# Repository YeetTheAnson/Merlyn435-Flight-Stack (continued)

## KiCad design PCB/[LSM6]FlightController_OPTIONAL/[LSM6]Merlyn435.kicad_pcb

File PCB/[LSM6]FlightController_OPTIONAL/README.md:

Almomst identical to the MPU6500 version of the board, but the footprint is changed to support LSM6 (LSM6DSK320X/LSM6DSV16X/LSM6DSO/LSM6DSOX) series gyro which has superior noise rejection compared to MPU6500 in high vibration environments.

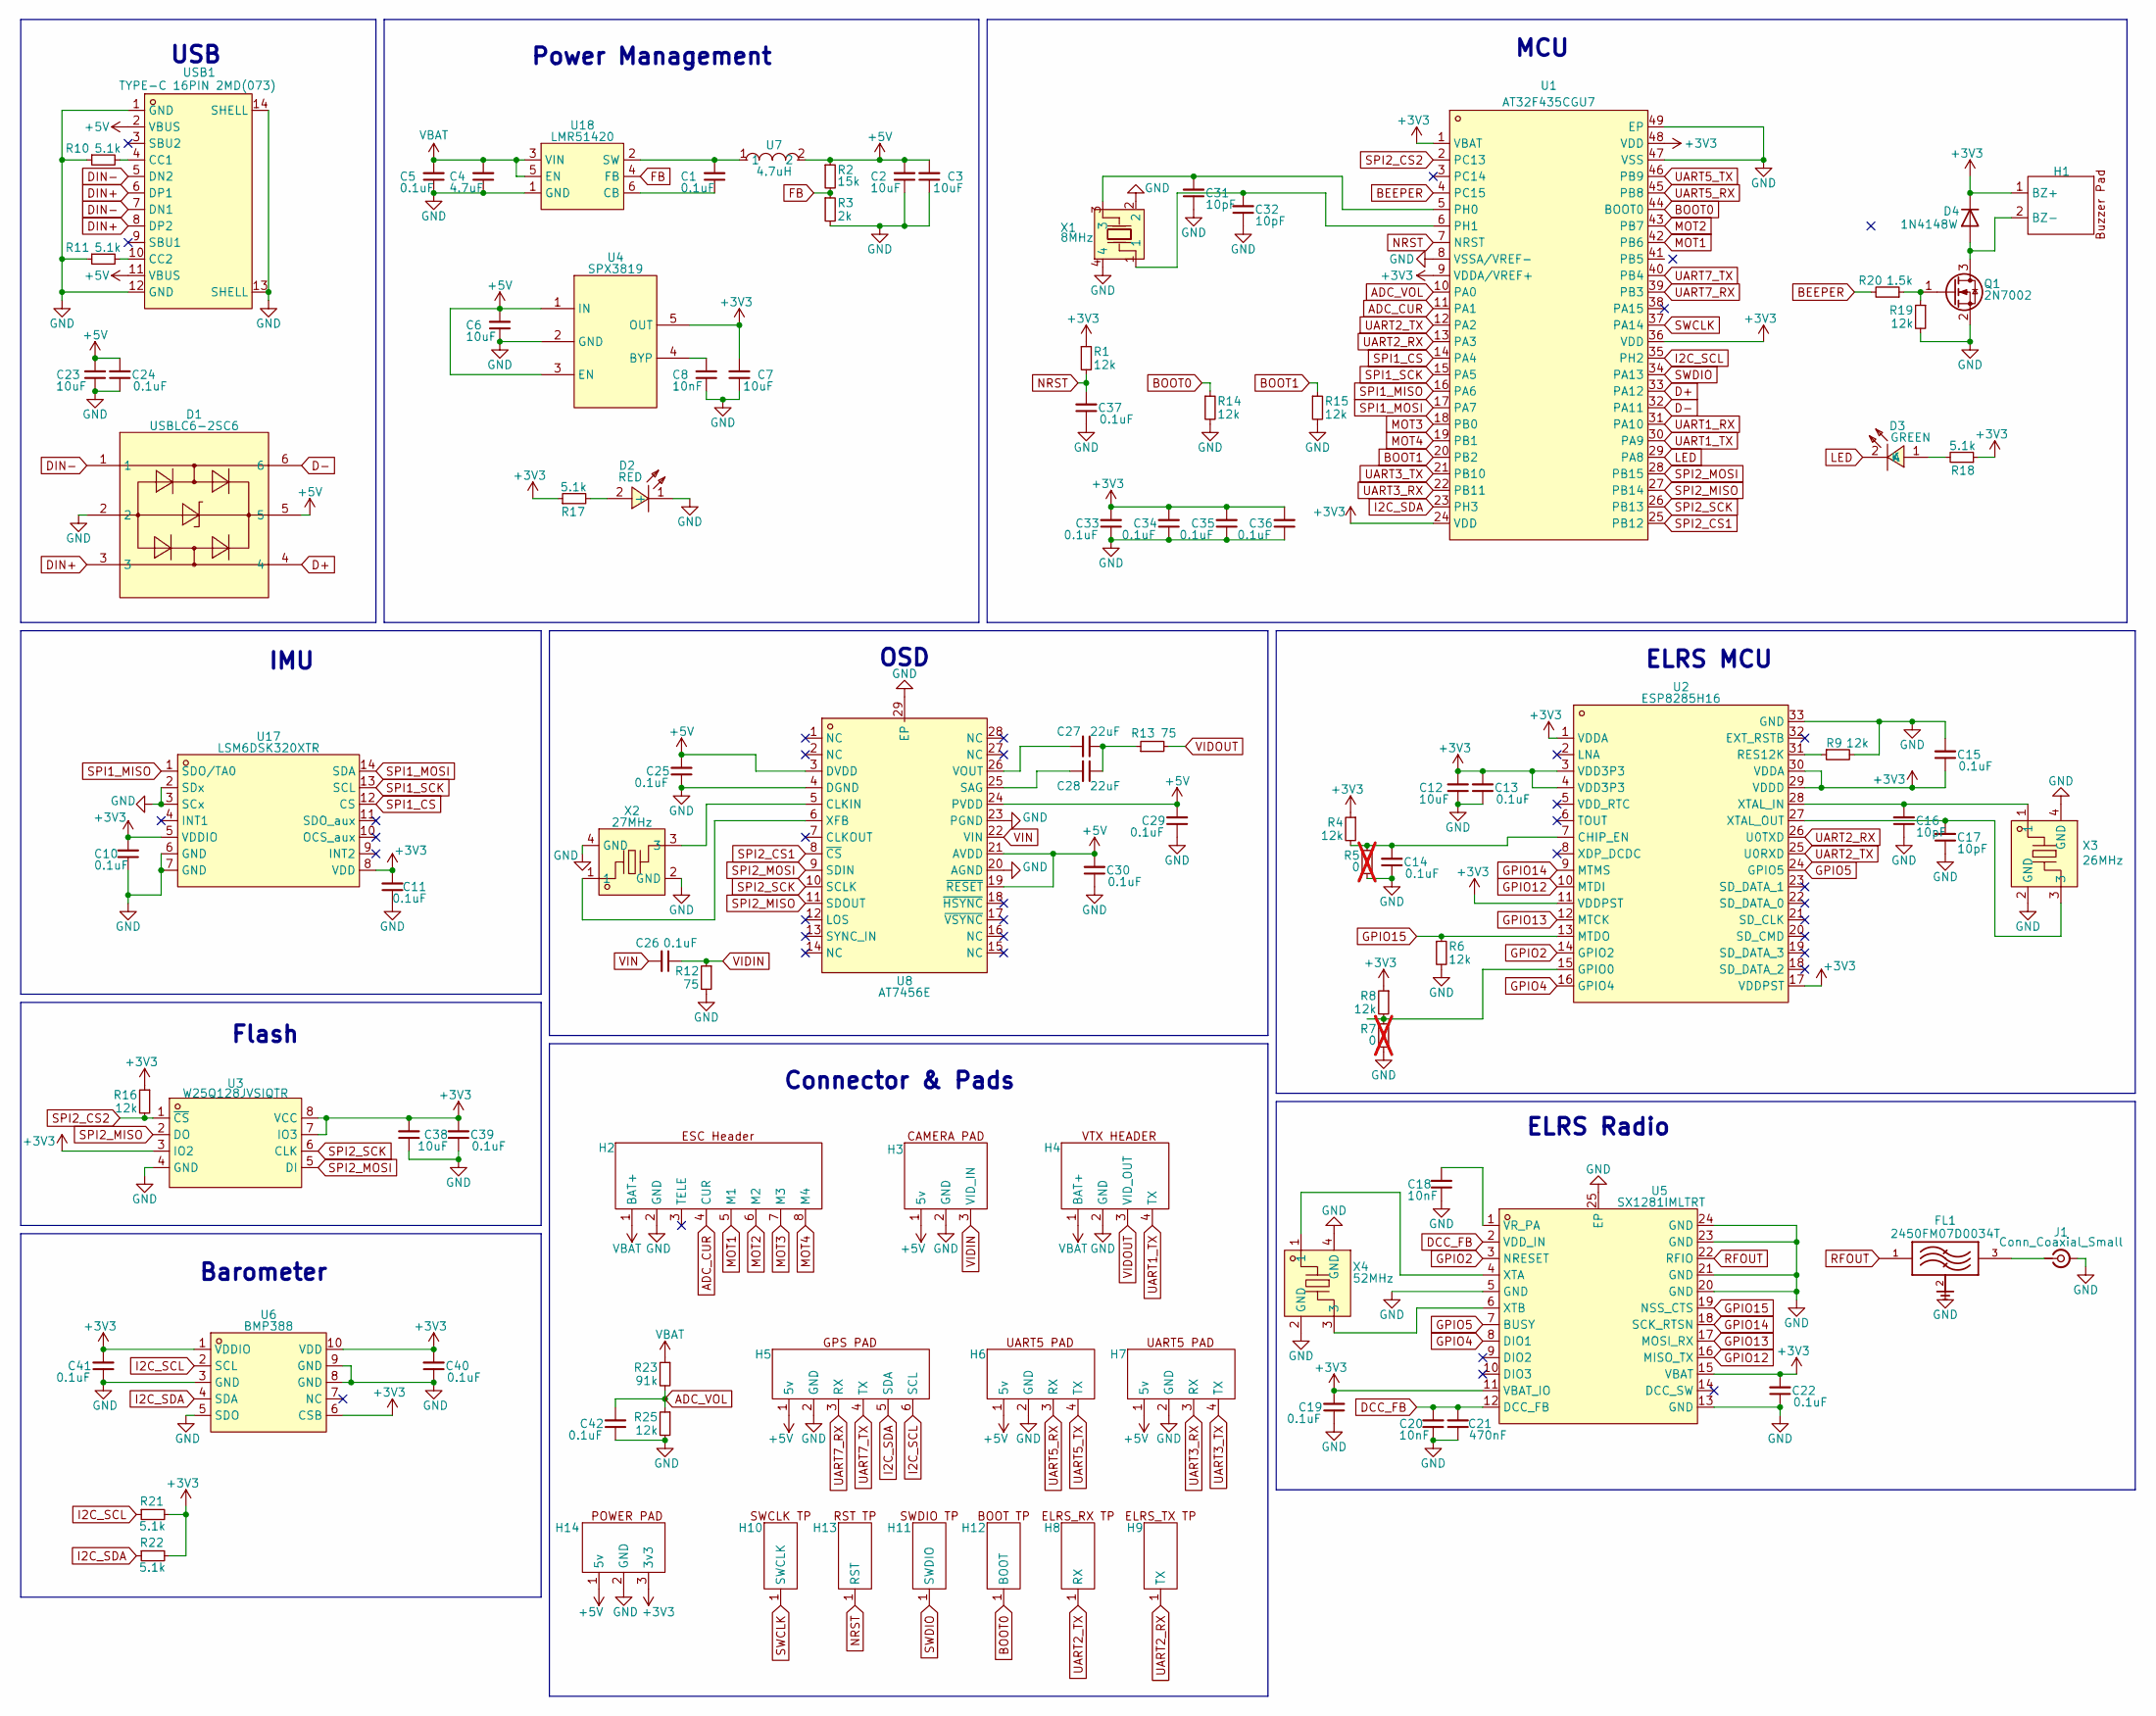
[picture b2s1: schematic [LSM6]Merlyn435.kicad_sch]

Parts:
C1, C5, C10, C11, C13, C14, C15, C19, C22, C24, C25, C26, C29, C30, C33, C34, C35, C36, C37, C39, C40, C41, C42: 0.1uF; C_0402_1005Metric; LCSC Part C307331
C2, C3, C6, C7: 10uF; C_0603_1608Metric; LCSC Part C96446
C4: 4.7uF; C_1206_3216Metric; LCSC Part C29823
C8, C18, C20: 10nF; C_0402_1005Metric; LCSC Part C15195
C12, C23, C38: 10uF; C_0402_1005Metric; LCSC Part C15525
C16, C17, C31, C32: 10pF; C_0402_1005Metric; LCSC Part C32949
C21: 470nF; C_0402_1005Metric; LCSC Part C47339
C27, C28: 22uF; C_0805_2012Metric; LCSC Part C45783
D1: USBLC6-2SC6; SOT-23-6_L2.9-W1.6-P0.95-LS2.8-BL; MPN USBLC6-2SC6; LCSC Part C7519
D2: RED; LED0805-RD; MPN NCD0805R1; LCSC Part C84256
D3: GREEN; LED0805-R-RD; MPN KT-0805G; LCSC Part C2297
D4: 1N4148W; D_SOD-123
FL1: 2450FM07D0034T; FIL_2450FM07D0034T; PARTREV 1.2
H1: Buzzer Pad
H2: ESC Header
H3: Camera Pad
H4: VTX Pad
H5: GPS Pad
H6: UART5 PAD
H7: UART3 PAD
H8: ELRS_RX TP
H9: ELRS_TX TP
H10: SWCLK TP
H11: SWDIO TP
H12: SWD_BOOT TP
H13: SWD_RST TP
H14: Power Pad
J1: Conn_Coaxial_Small; UFL
Q1: 2N7002; SOT-23
R1, R4, R6, R8, R9, R14, R15, R16, R19, R25: 12k; R_0402_1005Metric; LCSC Part C25752
R2: 15k; R_0402_1005Metric; LCSC Part C25756
R3: 2k; R_0402_1005Metric; LCSC Part C4109
R5, R7: 0; R_0402_1005Metric; not fitted
R10, R11, R17, R18, R21, R22: 5.1k; R_0402_1005Metric; LCSC Part C25905
R12, R13: 75; R_0402_1005Metric; LCSC Part C25133
R20: 1.5k; R_0402_1005Metric; LCSC Part C25867
R23: 91k; R_0603_1608Metric; LCSC Part C23265
U1: AT32F435CGU7; QFN-48_L6.0-W6.0-P0.40-TL-EP3.2; MPN AT32F435CGU7; LCSC Part C5178937
U2: ESP8285H16; QFN-32_L5.0-W5.0-P0.50-TL-EP3.7; MPN ESP8285H16; LCSC Part C967019
U3: W25Q128JVSIQTR; SOIC-8_L5.3-W5.3-P1.27-LS8.0-BL; MPN W25Q128JVSIQ; LCSC Part C97521
U4: SPX3819; SOT-23-5_L3.0-W1.7-P0.95-LS2.8-BL; MPN SPX3819M5-L-3-3/TR; LCSC Part C9055
U5: SX1281IMLTRT; QFN-24_L4.0-W4.0-P0.50-TL-EP2.6; MPN SX1281IMLTRT; LCSC Part C2151551
U6: BMP388; LGA-10_L2.0-W2.0-P0.50-BL; MPN BMP388(TOKMAS); LCSC Part C54582187
U7: 4.7uH; IND-SMD_L4.4-W4.2; MPN APH0420T4R7M; LCSC Part C5349668
U8: AT7456E; TSSOP-28_L9.7-W4.4-P0.65-LS6.4-BL-EP-2; MPN AT7456E; LCSC Part C82351
U17: LSM6DSK320XTR; LGA-14_L3.0-W2.5-P0.50-TL; MPN LSM6DSK320XTR; LCSC Part C53025794
U18: LMR51420; SOT-23-6_L2.9-W1.6-P0.95-LS2.9-BL; MPN LMR51420YDDCR; LCSC Part C5383002
USB1: TYPE-C 16PIN 2MD(073); USB-TYPE-C-SMD_TYPE-C-16P-QTWT; LCSC Part C5187472
X1: 8MHz; CRYSTAL-SMD_4P-L3.2-W2.5-BL; MPN TAXM8M4RDBCCT2T; LCSC Part C400090
X2: 27MHz; CRYSTAL-SMD_4P-L2.0-W1.6-BL; MPN 7D027000I01; LCSC Part C648950
X3: 26MHz; CRYSTAL-SMD_4P-L2.0-W1.6-BL; MPN XL7EL89CMI-111YLC-26M; LCSC Part C19272774
X4: 52MHz; CRYSTAL-SMD_4P-L2.0-W1.6-BL; MPN XC21M4-52.000-F10NNHPL; LCSC Part C3034316

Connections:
+3V3: C7.2, C10.2, C11.2, C12.2, C13.2, C15.1, C19.2, C22.2, C33.2, C34.2, C35.2, C36.2, C38.2, C39.2, C40.2, C41.2, D4.1 (K), H1.1 (BZ+), H14.3 (3v3), R1.1, R4.1, R8.1, R16.1, R17.1, R18.1, R21.2, R22.2, U1.1 (VBAT), U1.9 (VDDA/VREF+), U1.24 (VDD), U1.36 (VDD), U1.48 (VDD), U2.1 (VDDA), U2.3 (VDD3P3), U2.4 (VDD3P3), U2.11 (VDDPST), U2.17 (VDDPST), U2.29 (VDDD), U2.30 (VDDA), U3.3 (IO2), U3.7 (IO3), U3.8 (VCC), U4.5 (OUT), U5.11 (VBAT_IO), U5.15 (VBAT), U6.1 (VDDIO), U6.6 (CSB), U6.10 (VDD), U17.5 (VDDIO), U17.8 (VDD)
+5V: C2.2, C3.2, C6.2, C23.2, C24.2, C25.2, C29.2, C30.2, D1.5, H3.1 (5v), H5.1 (5v), H6.1 (5v), H7.1 (5v), H14.1 (5v), R2.1, U4.1 (IN), U4.3 (EN), U7.2, U8.3 (DVDD), U8.19 (~RESET), U8.21 (AVDD), U8.24 (PVDD), USB1.2 (VBUS), USB1.11 (VBUS)
ADC_CUR: H2.4 (CUR), U1.11 (PA1)
ADC_VOL: C42.2, R23.2, R25.1, U1.10 (PA0)
BEEPER: R20.2, U1.4 (PC15)
BOOT0: H12.1 (BOOT), R14.1, U1.44 (BOOT0)
BOOT1: R15.1, U1.20 (PB2)
D+: D1.4, U1.33 (PA12)
D-: D1.6, U1.32 (PA11)
DCC_FB: C20.2, C21.2, U5.2 (VDD_IN), U5.12 (DCC_FB)
DIN+: D1.3, USB1.6 (DP1), USB1.8 (DP2)
DIN-: D1.1, USB1.5 (DN2), USB1.7 (DN1)
FB: R2.2, R3.1, U18.4 (FB)
GND: C2.1, C3.1, C4.1, C5.1, C6.1, C7.1, C8.1, C10.1, C11.1, C12.1, C13.1, C14.1, C15.2, C16.1, C17.1, C18.1, C19.1, C20.1, C21.1, C22.1, C23.1, C24.1, C25.1, C29.1, C30.1, C31.1, C32.1, C33.1, C34.1, C35.1, C36.1, C37.1, C38.1, C39.1, C40.1, C41.1, C42.1, D1.2, D2.1 (-), FL1.2, FL1.4, H2.2 (GND), H3.2 (GND), H4.2 (GND), H5.2 (GND), H6.2 (GND), H7.2 (GND), H14.2 (GND), J1.2 (Ext), Q1.2 (S), R3.2, R5.2, R6.2, R7.2, R9.2, R10.1, R11.1, R12.2, R14.2, R15.2, R19.2, R25.2, U1.8 (VSSA/VREF-), U1.47 (VSS), U1.49 (EP), U2.33 (GND), U3.4 (GND), U4.2 (GND), U5.5 (GND), U5.13 (GND), U5.20 (GND), U5.21 (GND), U5.23 (GND), U5.24 (GND), U5.25 (EP), U6.3 (GND), U6.5 (SDO), U6.8 (GND), U6.9 (GND), U8.4 (DGND), U8.20 (AGND), U8.23 (PGND), U8.29 (EP), U17.2 (SDx), U17.3 (SCx), U17.6 (GND), U17.7 (GND), U18.1 (GND), USB1.1 (GND), USB1.12 (GND), USB1.13 (SHELL), USB1.14 (SHELL), X1.2, X1.4, X2.2 (GND), X2.4 (GND), X3.2 (GND), X3.4 (GND), X4.2 (GND), X4.4 (GND)
GPIO2: U2.14 (GPIO2), U5.3 (NRESET)
GPIO4: U2.16 (GPIO4), U5.8 (DIO1)
GPIO5: U2.24 (GPIO5), U5.7 (BUSY)
GPIO12: U2.10 (MTDI), U5.16 (MISO_TX)
GPIO13: U2.12 (MTCK), U5.17 (MOSI_RX)
GPIO14: U2.9 (MTMS), U5.18 (SCK_RTSN)
GPIO15: R6.1, U2.13 (MTDO), U5.19 (NSS_CTS)
I2C_SCL: H5.6 (SCL), R21.1, U1.35 (PH2), U6.2 (SCL)
I2C_SDA: H5.5 (SDA), R22.1, U1.23 (PH3), U6.4 (SDA)
LED: D3.2 (K), U1.29 (PA8)
MOT1: H2.5 (M1), U1.42 (PB6)
MOT2: H2.6 (M2), U1.43 (PB7)
MOT3: H2.7 (M3), U1.18 (PB0)
MOT4: H2.8 (M4), U1.19 (PB1)
NRST: C37.2, H13.1 (RST), R1.2, U1.7 (NRST)
unnamed: C27.1, C28.1, R13.1
unnamed: D2.2 (+), R17.2
unnamed: D3.1 (A), R18.2
unnamed: D4.2 (A), H1.2 (BZ-), Q1.3 (D)
unnamed: FL1.3, J1.1 (In)
unnamed: Q1.1 (G), R19.1, R20.1
unnamed: C31.2, U1.5 (PH0), X1.3
unnamed: C32.2, U1.6 (PH1), X1.1
unnamed: C14.2, R4.2, R5.1, U2.7 (CHIP_EN)
unnamed: R7.1, R8.2, U2.15 (GPIO0)
unnamed: R9.1, U2.31 (RES12K)
unnamed: C16.2, U2.28 (XTAL_IN), X3.1
unnamed: C17.2, U2.27 (XTAL_OUT), X3.3
unnamed: C8.2, U4.4 (BYP)
unnamed: C18.2, U5.1 (VR_PA)
unnamed: U5.4 (XTA), X4.1
unnamed: U5.6 (XTB), X4.3
unnamed: U8.5 (CLKIN), X2.3
unnamed: C28.2, U8.25 (SAG)
unnamed: C27.2, U8.26 (VOUT)
unnamed: U8.6 (XFB), X2.1
unnamed: C1.1, U18.6 (CB)
unnamed: C1.2, U7.1, U18.2 (SW)
unnamed: R10.2, USB1.4 (CC1)
unnamed: R11.2, USB1.10 (CC2)
RFOUT: FL1.1, U5.22 (RFIO)
SPI1_CS: U1.14 (PA4), U17.12 (CS)
SPI1_MISO: U1.16 (PA6), U17.1 (SDO/TA0)
SPI1_MOSI: U1.17 (PA7), U17.14 (SDA)
SPI1_SCK: U1.15 (PA5), U17.13 (SCL)
SPI2_CS1: U1.25 (PB12), U8.8 (~CS)
SPI2_CS2: R16.2, U1.2 (PC13), U3.1 (~CS)
SPI2_MISO: U1.27 (PB14), U3.2 (DO), U8.11 (SDOUT)
SPI2_MOSI: U1.28 (PB15), U3.5 (DI), U8.9 (SDIN)
SPI2_SCK: U1.26 (PB13), U3.6 (CLK), U8.10 (SCLK)
SWCLK: H10.1 (SWCLK), U1.37 (PA14)
SWDIO: H11.1 (SWDIO), U1.34 (PA13)
UART1_RX: U1.31 (PA10)
UART1_TX: H4.4 (TX), U1.30 (PA9)
UART2_RX: H9.1 (TX), U1.13 (PA3), U2.26 (U0TXD)
UART2_TX: H8.1 (RX), U1.12 (PA2), U2.25 (U0RXD)
UART3_RX: H7.3 (RX), U1.22 (PB11)
UART3_TX: H7.4 (TX), U1.21 (PB10)
UART5_RX: H6.3 (RX), U1.45 (PB8)
UART5_TX: H6.4 (TX), U1.46 (PB9)
UART7_RX: H5.3 (RX), U1.39 (PB3)
UART7_TX: H5.4 (TX), U1.40 (PB4)
VBAT: C4.2, C5.2, H2.1 (BAT+), H4.1 (BAT+), R23.1, U18.3 (VIN), U18.5 (EN)
VIDIN: C26.1, H3.3 (VID_IN), R12.1
VIDOUT: H4.3 (VID_OUT), R13.2
VIN: C26.2, U8.22 (VIN)

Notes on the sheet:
Barometer
USB
Power Management
ELRS Radio
Connector & Pads
MCU
ELRS MCU
OSD
IMU
Flash

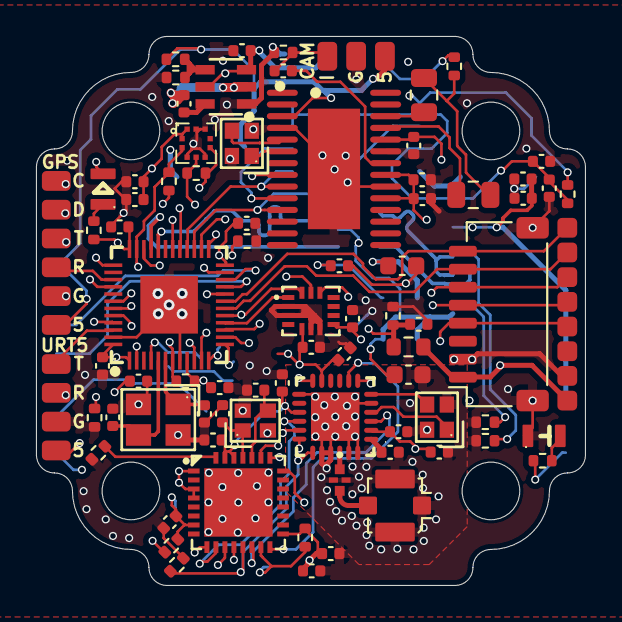
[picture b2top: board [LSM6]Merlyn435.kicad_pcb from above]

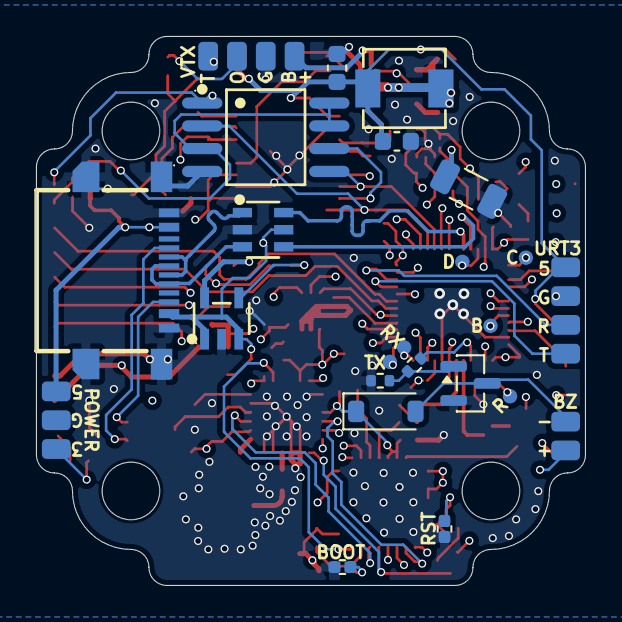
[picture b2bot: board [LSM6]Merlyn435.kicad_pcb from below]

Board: 4 copper layers, 30.5 x 30.5 mm, 101 parts (24 on the bottom side), 79 nets.

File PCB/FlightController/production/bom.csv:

Designator,Footprint,Quantity,Value,LCSC Part #
"C1, C10, C11, C13, C14, C15, C19, C22, C24, C25, C26, C29, C30, C33, C34, C35, C36, C37, C39, C40, C41, C42, C5",0402,23,0.1uF,C307331
"C12, C23, C38",0402,3,10uF,C15525
"C16, C17, C31, C32",0402,4,10pF,C32949
"C18, C20, C8, C9",0402,4,10nF,C15195
"C2, C3, C6, C7",0603,4,10uF,C96446
C21,0402,1,470nF,C47339
"C27, C28",0805,2,22uF,C45783
C4,1206,1,4.7uF,C29823 
D1,SOT-23-6_L2.9-W1.6-P0.95-LS2.8-BL,1,USBLC6-2SC6,C7519
D2,LED0805-RD,1,RED,C84256
D3,LED0805-R-RD,1,GREEN,C2297
D4,D_SOD-123,1,1N4148W,
H1,Buzzer Pad,1,~,
H10,SWCLK TP,1,~,
H11,SWDIO TP,1,~,
H12,SWD_BOOT TP,1,~,
H13,SWD_RST TP,1,~,
H14,Power Pad,1,~,
H2,ESC Header,1,~,
H3,Camera Pad,1,~,
H4,VTX Pad,1,~,
H5,GPS Pad,1,~,
H6,UART5 PAD,1,~,
H7,UART3 PAD,1,~,
H8,ELRS_RX TP,1,~,
H9,ELRS_TX TP,1,~,
Q1,SOT-23,1,2N7002,
"R1, R14, R15, R16, R19, R25, R4, R6, R8, R9",0402,10,12k,C25752
"R10, R11, R17, R18, R21, R22",0402,6,5.1k,C25905
"R12, R13",0402,2,75,C25133
R2,0402,1,15k,C25756
R20,0402,1,1.5k,C25867
R23,0603,1,91k,C23265
R3,0402,1,2k,C4109
U1,QFN-48_L6.0-W6.0-P0.40-TL-EP3.2,1,AT32F435CGU7,C5178937
U17,QFN-24_L3.0-W3.0-P0.40-BL-EP,1,MPU6500,C50278
U18,SOT-23-6_L2.9-W1.6-P0.95-LS2.9-BL,1,LMR51420,C5383002
U2,QFN-32_L5.0-W5.0-P0.50-TL-EP3.7,1,ESP8285H16,C967019
U3,SOIC-8_L5.3-W5.3-P1.27-LS8.0-BL,1,W25Q128JVSIQTR,C97521
U4,SOT-23-5_L3.0-W1.7-P0.95-LS2.8-BL,1,SPX3819,C9055
U5,QFN-24_L4.0-W4.0-P0.50-TL-EP2.6,1,SX1281IMLTRT,C2151551
U6,LGA-10_L2.0-W2.0-P0.50-BL,1,BMP388,C54582187
U7,IND-SMD_L4.4-W4.2,1,4.7uH,C5349668
U8,TSSOP-28_L9.7-W4.4-P0.65-LS6.4-BL-EP-2,1,AT7456E,C82351
USB1,USB-TYPE-C-SMD_TYPE-C-16P-QTWT,1,TYPE-C 16PIN 2MD(073),C2765186
X1,CRYSTAL-SMD_4P-L3.2-W2.5-BL,1,8MHz,C400090
X2,CRYSTAL-SMD_4P-L2.0-W1.6-BL,1,27MHz,C648950
X3,CRYSTAL-SMD_4P-L2.0-W1.6-BL,1,26MHz,C19272774
X4,CRYSTAL-SMD_4P-L2.0-W1.6-BL,1,52MHz,C3034316

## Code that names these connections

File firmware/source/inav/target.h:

#pragma once

#define TARGET_BOARD_IDENTIFIER "MERL"
#define USBD_PRODUCT_STRING     "MERLYN435"

// ---- IO PORTS ----
#define TARGET_IO_PORTA         0xffff
#define TARGET_IO_PORTB         0xffff
#define TARGET_IO_PORTC         0xffff
#define TARGET_IO_PORTH         0xffff

// ---- PIN MAPPING ----
#define LED0                    PA8
#define LED0_INVERTED
#define BEEPER                  PC15
#define BEEPER_INVERTED

// ---- SPI 1 (IMU) ----
#define USE_SPI
#define USE_SPI_DEVICE_1
#define SPI1_SCK_PIN            PA5
#define SPI1_MISO_PIN           PA6
#define SPI1_MOSI_PIN           PA7
#define SPI1_NSS_PIN            PA4
#define USE_IMU_MPU6500
#define IMU_MPU6500_ALIGN       CW0_DEG
#define MPU6500_SPI_BUS         BUS_SPI1
#define MPU6500_CS_PIN          SPI1_NSS_PIN

#define USE_IMU_LSM6DXX
#define IMU_LSM6DXX_ALIGN       CW0_DEG
#define LSM6DXX_SPI_BUS         BUS_SPI1
#define LSM6DXX_CS_PIN          SPI1_NSS_PIN

// ---- SPI 2 (OSD & FLASH) ----
#define USE_SPI_DEVICE_2
#define SPI2_SCK_PIN            PB13
#define SPI2_MISO_PIN           PB14
#define SPI2_MOSI_PIN           PB15
#define SPI2_NSS_PIN            PB12

#define USE_MAX7456
#define MAX7456_SPI_BUS         BUS_SPI2
#define MAX7456_CS_PIN          PB12

#define USE_FLASHFS
#define USE_FLASH_M25P16
#define M25P16_SPI_BUS          BUS_SPI2
#define M25P16_CS_PIN           PC13

// ---- I2C (Baro) ----
#define USE_I2C
#define USE_I2C_DEVICE_2
#define I2C2_SCL                PH2
#define I2C2_SDA                PH3

#define DEFAULT_I2C_BUS         BUS_I2C2
#define USE_BARO
#define BARO_I2C_BUS            BUS_I2C2
#define USE_BARO_BMP388

// ---- ADC ----
#define USE_ADC
#define ADC_INSTANCE                ADC1
#define ADC1_DMA_STREAM             DMA2_CHANNEL1
#define ADC_CHANNEL_1_PIN           PA0
#define ADC_CHANNEL_2_PIN           PA1
#define VBAT_ADC_CHANNEL            ADC_CHN_1
#define CURRENT_METER_ADC_CHANNEL   ADC_CHN_2

// ---- USB ----
#define USE_VCP
#define USE_USB_DETECT

// ---- UARTS ----
#define USE_UART1
#define UART1_TX_PIN            PA9
#define UART1_RX_PIN            PA10

#define USE_UART2
#define UART2_TX_PIN            PA2
#define UART2_RX_PIN            PA3

#define USE_UART3
#define UART3_TX_PIN            PB10
#define UART3_RX_PIN            PB11

#define USE_UART5
#define UART5_TX_PIN            PB9
#define UART5_RX_PIN            PB8

#define USE_UART7
#define UART7_TX_PIN            PB4
#define UART7_RX_PIN            PB3

#define SERIAL_PORT_COUNT       5
#define DEFAULT_RX_TYPE         RX_TYPE_SERIAL
#define SERIALRX_PROVIDER       SERIALRX_CRSF
#define SERIALRX_UART           SERIAL_PORT_USART2

// ---- DEFAULTS & EXTENDED FEATURES ----
#define DEFAULT_FEATURES        (FEATURE_OSD | FEATURE_VBAT | FEATURE_CURRENT_METER)
#define MAX_PWM_OUTPUT_PORTS    4
#define USE_DSHOT
#define USE_ESC_SENSOR          
#define USE_CRASH_FLIP          
#define USE_RPM_FILTER

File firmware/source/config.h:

/*
 * This file is part of Betaflight.
 *
 * Betaflight is free software. You can redistribute this software
 * and/or modify this software under the terms of the GNU General
 * Public License as published by the Free Software Foundation,
 * either version 3 of the License, or (at your option) any later
 * version.
 *
 * Betaflight is distributed in the hope that it will be useful,
 * but WITHOUT ANY WARRANTY; without even the implied warranty of
 * MERCHANTABILITY or FITNESS FOR A PARTICULAR PURPOSE.
 *
 * See the GNU General Public License for more details.
 *
 * You should have received a copy of the GNU General Public
 * License along with this software.
 *
 * If not, see <http://www.gnu.org/licenses/>.
 */

#pragma once

#define FC_TARGET_MCU        AT32F435G

#define BOARD_NAME           MERLYN435
#define MANUFACTURER_ID      ANSON

// ---- CLOCK ----
#define SYSTEM_HSE_MHZ       8

// ---- INTERNAL COMPONENTS ----
#define USE_ACC
#define USE_GYRO
#define USE_ACC_SPI_MPU6500
#define USE_GYRO_SPI_MPU6500

#define USE_BARO
#define USE_BARO_BMP388

#define USE_MAX7456

#define USE_FLASH
#define USE_FLASH_W25Q128FV

// ---- PIN MAPPING ----
#define LED0_PIN             PA8
#define BEEPER_PIN           PC15
#define BEEPER_INVERTED

// ---- ADC ----
#define USE_ADC
#define ADC_VBAT_PIN         PA0
#define ADC_CURR_PIN         PA1
#define ADC_INSTANCE         ADC1
#define ADC1_DMA_OPT         11

// ---- MOTORS ----
#define MOTOR1_PIN           PB6
#define MOTOR2_PIN           PB7
#define MOTOR3_PIN           PB0
#define MOTOR4_PIN           PB1

// ---- UARTS ----
#define UART1_TX_PIN         PA9
#define UART1_RX_PIN         PA10
#define UART2_TX_PIN         PA2
#define UART2_RX_PIN         PA3
#define UART3_TX_PIN         PB10
#define UART3_RX_PIN         PB11
#define UART5_TX_PIN         PB9
#define UART5_RX_PIN         PB8
#define UART7_TX_PIN         PB4
#define UART7_RX_PIN         PB3

// ---- I2C (External + BMP388) ----
#define I2C2_SCL_PIN         PH2
#define I2C2_SDA_PIN         PH3

// ---- SPI1 (MPU6500) ----
#define SPI1_SCK_PIN         PA5
#define SPI1_SDI_PIN         PA6
#define SPI1_SDO_PIN         PA7

// ---- SPI2 (Flash & OSD) ----
#define SPI2_SCK_PIN         PB13
#define SPI2_SDI_PIN         PB14
#define SPI2_SDO_PIN         PB15

// ---- CHIP SELECTS ----
#define GYRO_1_CS_PIN        PA4
#define MAX7456_SPI_CS_PIN   PB12
#define FLASH_CS_PIN         PC13

// ---- HARDWARE INSTANCES ----
#define GYRO_1_SPI_INSTANCE  SPI1
#define FLASH_SPI_INSTANCE   SPI2
#define MAX7456_SPI_INSTANCE SPI2
#define BARO_I2C_INSTANCE    I2CDEV_2
#define MAG_I2C_INSTANCE     I2CDEV_2

// ---- TIMER MAPPING ----
#define TIMER_PIN_MAPPING \
    TIMER_PIN_MAP( 0, PB6, 1,  0) \
    TIMER_PIN_MAP( 1, PB7, 1,  1) \
    TIMER_PIN_MAP( 2, PB0, 2,  2) \
    TIMER_PIN_MAP( 3, PB1, 2,  3)

// ---- DEFAULTS ----
#define DEFAULT_BLACKBOX_DEVICE         BLACKBOX_DEVICE_FLASH
#define DEFAULT_CURRENT_METER_SOURCE    CURRENT_METER_ADC
#define DEFAULT_VOLTAGE_METER_SOURCE    VOLTAGE_METER_ADC
#define DEFAULT_DSHOT_BITBANG           DSHOT_BITBANG_ON
#define DEFAULT_DSHOT_BURST             DSHOT_DMAR_AUTO

// Setting default ports for your layout logic
#define SERIALRX_UART                   SERIAL_PORT_USART2
